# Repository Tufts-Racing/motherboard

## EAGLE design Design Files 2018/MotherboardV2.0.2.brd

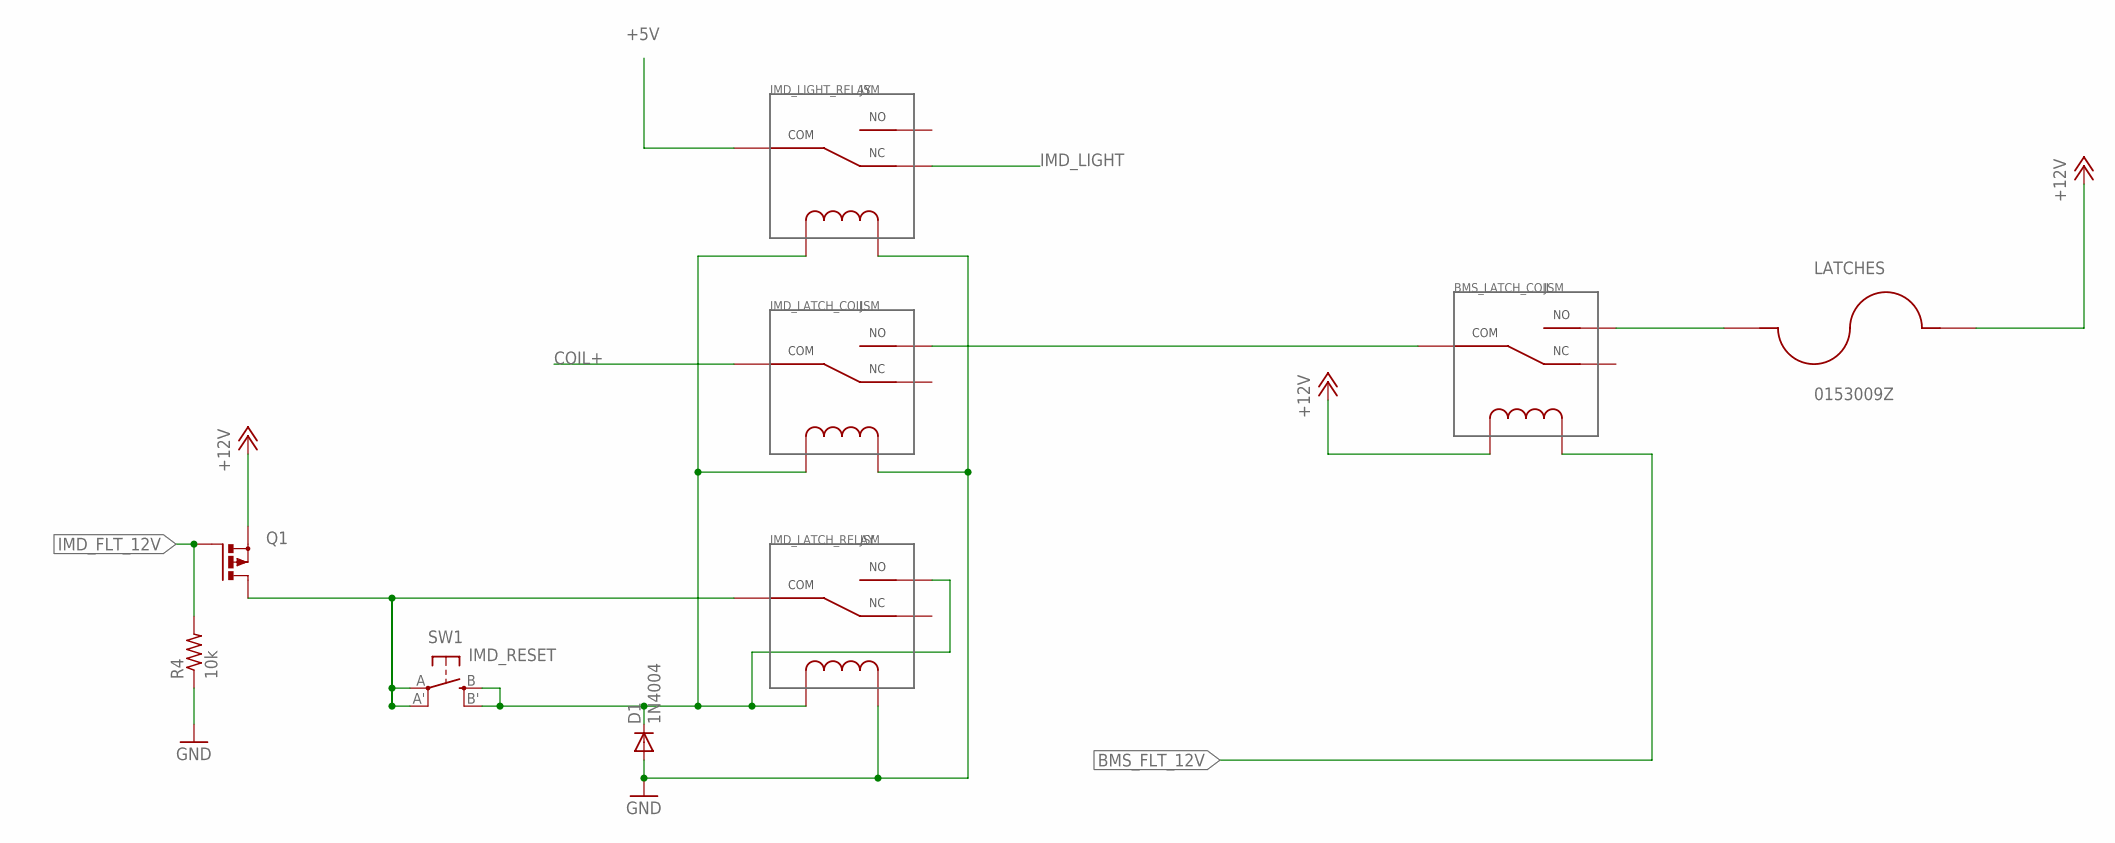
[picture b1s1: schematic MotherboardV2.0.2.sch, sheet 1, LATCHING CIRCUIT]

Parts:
BMS_LATCH_COIL: JSM; JS-M
D1: 1N4004; DO41-10
IMD_LATCH_COIL: JSM; JS-M
IMD_LATCH_RELAY: JSM; JS-M
IMD_LIGHT_RELAY: JSM; JS-M
LATCHES: 0153009Z; MINIFUSEHOLDER
Q1: PMOSFET_PTO220BV; TO220BV
R4: 10k; 0207/9
SW1: IMD_RESET; EVQ-Q2

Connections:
+5V: IMD_LIGHT_RELAY.COM; also elsewhere on the board
+12V: BMS_LATCH_COIL.COIL1, LATCHES.P$2, Q1.S; also elsewhere on the board
BMS_FLT_12V: BMS_LATCH_COIL.COIL2; also elsewhere on the board
COIL+: IMD_LATCH_COIL.COM; also elsewhere on the board
GND: D1.A, IMD_LATCH_COIL.COIL2, IMD_LATCH_RELAY.COIL2, IMD_LIGHT_RELAY.COIL2, R4.1; also elsewhere on the board
IMD_FLT_12V: Q1.G, R4.2; also elsewhere on the board
IMD_LATCH_SW1: IMD_LATCH_RELAY.COM, Q1.D, SW1.A, SW1.A' (P1)
IMD_LATCH_SW2: D1.C, IMD_LATCH_COIL.COIL1, IMD_LATCH_RELAY.COIL1, IMD_LATCH_RELAY.NO, IMD_LIGHT_RELAY.COIL1, SW1.B (S), SW1.B' (S1)
IMD_LIGHT: IMD_LIGHT_RELAY.NC; also elsewhere on the board
unnamed: BMS_LATCH_COIL.COM, IMD_LATCH_COIL.NO
unnamed: BMS_LATCH_COIL.NO, LATCHES.P$1

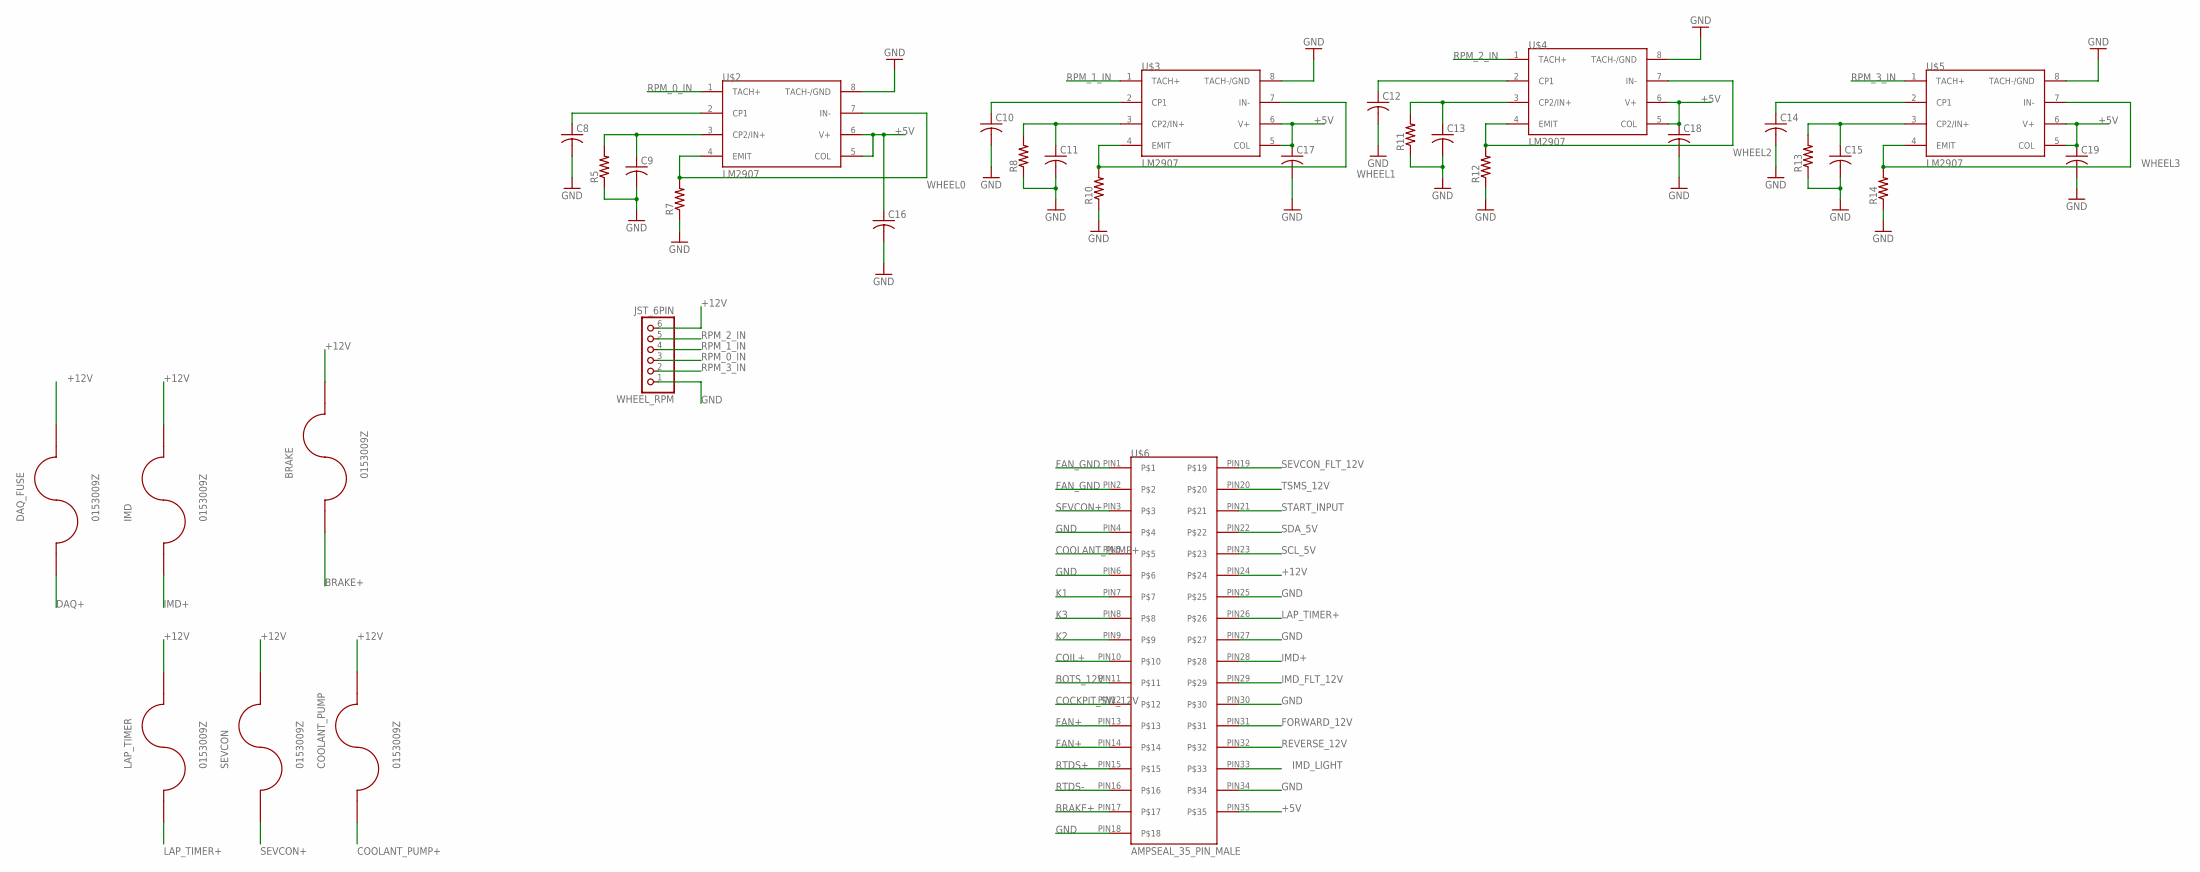
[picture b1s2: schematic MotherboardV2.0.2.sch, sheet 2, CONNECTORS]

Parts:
BRAKE: 0153009Z; MINIFUSEHOLDER
C8, C9, C10, C11, C12, C13, C14, C15, C16, C17, C18, C19: C-US050-024X044; C050-024X044
COOLANT_PUMP: 0153009Z; MINIFUSEHOLDER
DAQ_FUSE: 0153009Z; MINIFUSEHOLDER
IMD: 0153009Z; MINIFUSEHOLDER
LAP_TIMER: 0153009Z; MINIFUSEHOLDER
R5, R7, R8, R10, R11, R12, R13, R14: R-US_0309/V; 0309V
SEVCON: 0153009Z; MINIFUSEHOLDER
U$2, U$3, U$4, U$5: LM2907; DIL08
U$6: AMPSEAL_35_PIN_MALE
WHEEL_RPM: JST_6PIN; JST-PH-6-THM

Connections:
+5V: C16.1, C17.1, C18.1, C19.1, U$2.5 (COL), U$2.6 (V+), U$3.5 (COL), U$3.6 (V+), U$4.5 (COL), U$4.6 (V+), U$5.5 (COL), U$5.6 (V+), U$6.PIN35; also elsewhere on the board
+12V: BRAKE.P$2, COOLANT_PUMP.P$2, DAQ_FUSE.P$2, IMD.P$2, LAP_TIMER.P$2, SEVCON.P$2, U$6.PIN24, WHEEL_RPM.6; also elsewhere on the board
BOTS_12V: U$6.PIN11; also elsewhere on the board
BRAKE+: BRAKE.P$1, U$6.PIN17
COCKPIT_SW_12V: U$6.PIN12; also elsewhere on the board
COIL+: U$6.PIN10; also elsewhere on the board
COOLANT_PUMP+: COOLANT_PUMP.P$1, U$6.PIN5
DAQ+: DAQ_FUSE.P$1; also elsewhere on the board
FAN+: U$6.PIN13, U$6.PIN14; also elsewhere on the board
FAN_GND: U$6.PIN1, U$6.PIN2; also elsewhere on the board
FORWARD_12V: U$6.PIN31; also elsewhere on the board
GND: C8.2, C9.2, C10.2, C11.2, C12.2, C13.2, C14.2, C15.2, C16.2, C17.2, C18.2, C19.2, R5.1, R7.1, R8.1, R10.1, R11.1, R12.1, R13.1, R14.1, U$2.8 (TACH-/GND), U$3.8 (TACH-/GND), U$4.8 (TACH-/GND), U$5.8 (TACH-/GND), U$6.PIN4, U$6.PIN6, U$6.PIN18, U$6.PIN25, U$6.PIN27, U$6.PIN30, U$6.PIN34, WHEEL_RPM.1; also elsewhere on the board
IMD+: IMD.P$1, U$6.PIN28
IMD_FLT_12V: U$6.PIN29; also elsewhere on the board
IMD_LIGHT: U$6.PIN33; also elsewhere on the board
K1: U$6.PIN7; also elsewhere on the board
K2: U$6.PIN9; also elsewhere on the board
K3: U$6.PIN8; also elsewhere on the board
LAP_TIMER+: LAP_TIMER.P$1, U$6.PIN26
unnamed: C8.1, U$2.2 (CP1)
unnamed: C9.1, R5.2, U$2.3 (CP2/IN+)
unnamed: C10.1, U$3.2 (CP1)
unnamed: C11.1, R8.2, U$3.3 (CP2/IN+)
unnamed: C12.1, U$4.2 (CP1)
unnamed: C13.1, R11.2, U$4.3 (CP2/IN+)
unnamed: C14.1, U$5.2 (CP1)
unnamed: C15.1, R13.2, U$5.3 (CP2/IN+)
REVERSE_12V: U$6.PIN32; also elsewhere on the board
RPM_0_IN: U$2.1 (TACH+), WHEEL_RPM.3
RPM_1_IN: U$3.1 (TACH+), WHEEL_RPM.4
RPM_2_IN: U$4.1 (TACH+), WHEEL_RPM.5
RPM_3_IN: U$5.1 (TACH+), WHEEL_RPM.2
RTDS+: U$6.PIN15; also elsewhere on the board
RTDS-: U$6.PIN16; also elsewhere on the board
SCL_5V: U$6.PIN23; also elsewhere on the board
SDA_5V: U$6.PIN22; also elsewhere on the board
SEVCON+: SEVCON.P$1, U$6.PIN3
SEVCON_FLT_12V: U$6.PIN19; also elsewhere on the board
START_INPUT: U$6.PIN21; also elsewhere on the board
TSMS_12V: U$6.PIN20; also elsewhere on the board
WHEEL0: R7.2, U$2.4 (EMIT), U$2.7 (IN-); also elsewhere on the board
WHEEL1: R10.2, U$3.4 (EMIT), U$3.7 (IN-); also elsewhere on the board
WHEEL2: R12.2, U$4.4 (EMIT), U$4.7 (IN-); also elsewhere on the board
WHEEL3: R14.2, U$5.4 (EMIT), U$5.7 (IN-); also elsewhere on the board

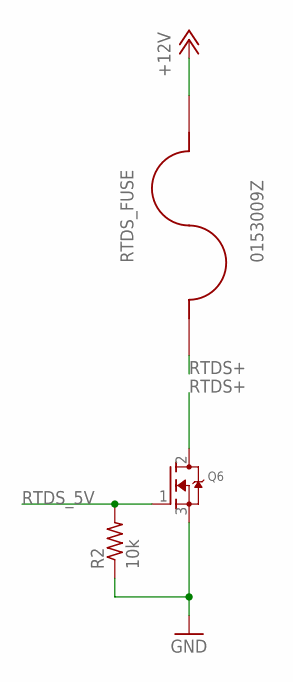
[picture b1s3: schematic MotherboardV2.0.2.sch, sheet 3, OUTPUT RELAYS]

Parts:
Q6: MOSFET-NGDS_TO220V; TO220V
R2: 10k; 0207/9
RTDS_FUSE: 0153009Z; MINIFUSEHOLDER

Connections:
+12V: RTDS_FUSE.P$2; also elsewhere on the board
GND: Q6.3 (S), R2.1; also elsewhere on the board
RTDS+: RTDS_FUSE.P$1; also elsewhere on the board
RTDS-: Q6.2 (D); also elsewhere on the board
RTDS_5V: Q6.1 (G), R2.2; also elsewhere on the board

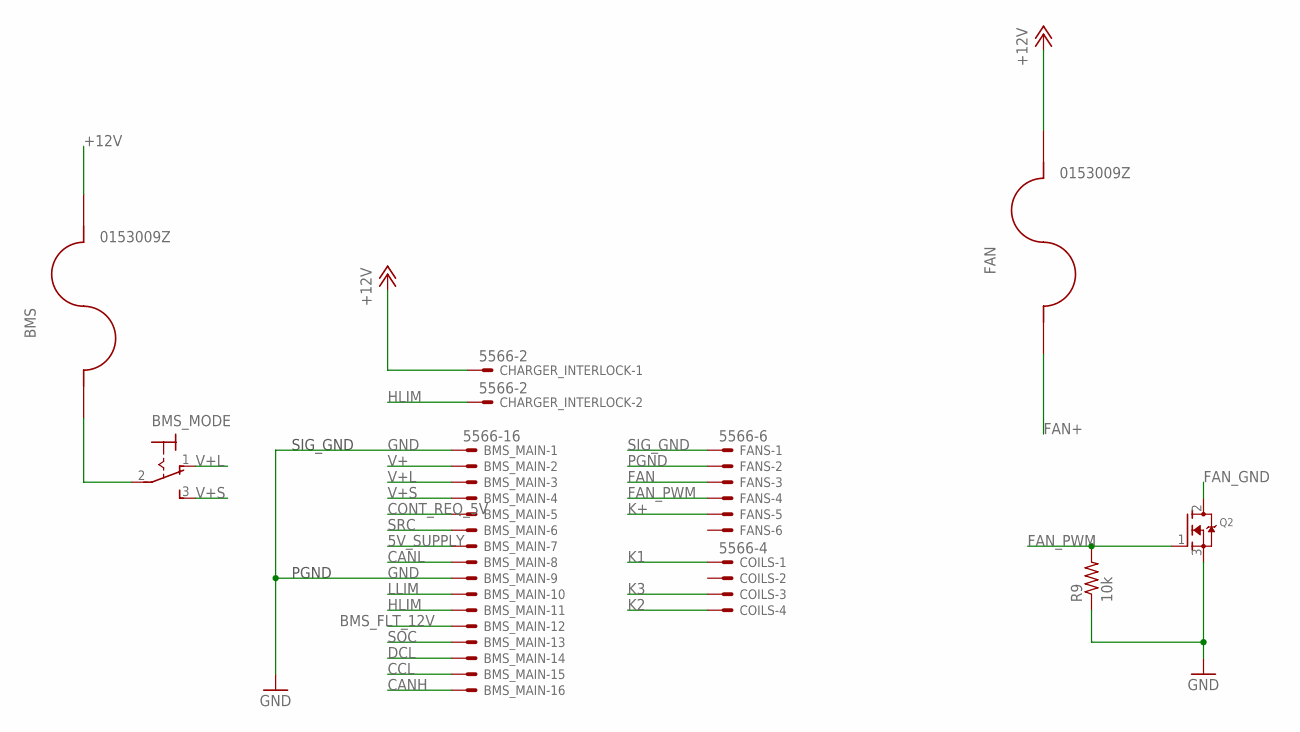
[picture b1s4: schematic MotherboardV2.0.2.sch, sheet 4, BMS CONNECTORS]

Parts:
BMS: 0153009Z; MINIFUSEHOLDER
BMS_MAIN: 5566-16
BMS_MODE: 320-916
CHARGER_INTERLOCK: 5566-2
COILS: 5566-4
FAN: 0153009Z; MINIFUSEHOLDER
FANS: 5566-6
Q2: MOSFET-NGDS_TO220V; TO220V
R9: 10k; 0207/9

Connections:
5V_SUPPLY: BMS_MAIN.7
+12V: BMS.P$2, CHARGER_INTERLOCK.1, FAN.P$2; also elsewhere on the board
BMS_FLT_12V: BMS_MAIN.12; also elsewhere on the board
CANH: BMS_MAIN.16
CANL: BMS_MAIN.8
CCL: BMS_MAIN.15
CONT_REQ_5V: BMS_MAIN.5; also elsewhere on the board
DCL: BMS_MAIN.14
FAN: FANS.3
FAN+: FAN.P$1; also elsewhere on the board
FAN_GND: Q2.2 (D); also elsewhere on the board
FAN_PWM: FANS.4, Q2.1 (G), R9.2
GND: BMS_MAIN.1, BMS_MAIN.9, Q2.3 (S), R9.1; also elsewhere on the board
HLIM: BMS_MAIN.11, CHARGER_INTERLOCK.2
K1: COILS.1; also elsewhere on the board
K2: COILS.4; also elsewhere on the board
K3: COILS.3; also elsewhere on the board
K+: FANS.5
LLIM: BMS_MAIN.10
unnamed: BMS.P$1, BMS_MODE.2
PGND: FANS.2
SIG_GND: FANS.1
SOC: BMS_MAIN.13; also elsewhere on the board
SRC: BMS_MAIN.6
V+: BMS_MAIN.2
V+L: BMS_MAIN.3, BMS_MODE.1 (O)
V+S: BMS_MAIN.4, BMS_MODE.3 (S)

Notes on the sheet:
SIG_GND
PGND

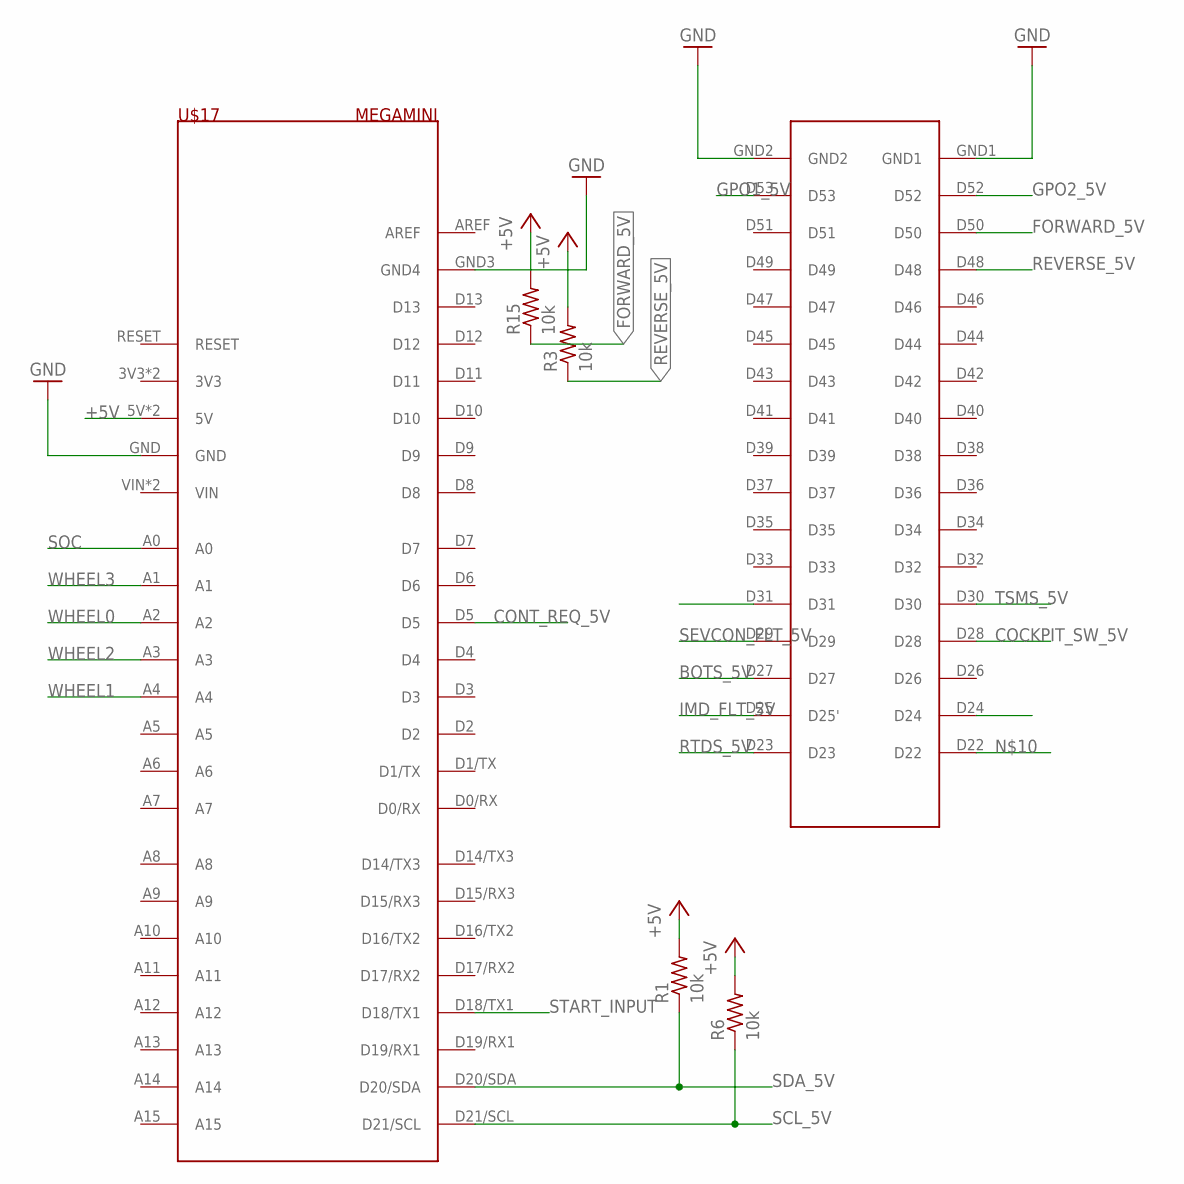
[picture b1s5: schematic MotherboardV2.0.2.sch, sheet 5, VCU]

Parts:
R1, R3, R6, R15: 10k; 0207/9
U$17: MEGAMINI

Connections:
+5V: R1.2, R3.2, R6.2, R15.2, U$17.5V, U$17.5V_2 (5V); also elsewhere on the board
BMS_FLT_5V: U$17.D31; also elsewhere on the board
BOTS_5V: U$17.D27; also elsewhere on the board
COCKPIT_SW_5V: U$17.D28; also elsewhere on the board
CONT_REQ_5V: U$17.D5; also elsewhere on the board
FORWARD_5V: R15.1, U$17.D50; also elsewhere on the board
GND: U$17.GND, U$17.GND1, U$17.GND2, U$17.GND3 (GND4); also elsewhere on the board
GPO1_5V: U$17.D53; also elsewhere on the board
GPO2_5V: U$17.D52; also elsewhere on the board
IMD_FLT_5V: U$17.D25 (D25'); also elsewhere on the board
REVERSE_5V: R3.1, U$17.D48; also elsewhere on the board
RTDS_5V: U$17.D23; also elsewhere on the board
SCL_5V: R6.1, U$17.D21/SCL; also elsewhere on the board
SDA_5V: R1.1, U$17.D20/SDA; also elsewhere on the board
SEVCON_FLT_5V: U$17.D29; also elsewhere on the board
SOC: U$17.A0; also elsewhere on the board
START_INPUT: U$17.D18/TX1; also elsewhere on the board
TSMS_5V: U$17.D30; also elsewhere on the board
WHEEL0: U$17.A2; also elsewhere on the board
WHEEL1: U$17.A4; also elsewhere on the board
WHEEL2: U$17.A3; also elsewhere on the board
WHEEL3: U$17.A1; also elsewhere on the board

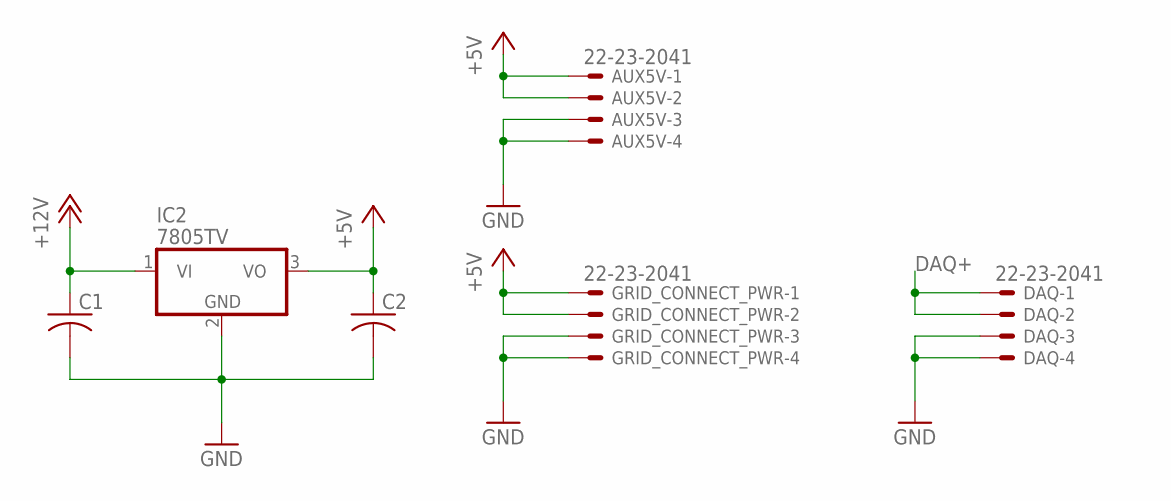
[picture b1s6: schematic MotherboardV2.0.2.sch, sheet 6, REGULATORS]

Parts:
AUX5V: 22-23-2041
C1, C2: C-US050-024X044; C050-024X044
DAQ: 22-23-2041
GRID_CONNECT_PWR: 22-23-2041
IC2: 7805TV; TO220V

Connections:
+5V: AUX5V.1, AUX5V.2, C2.1, GRID_CONNECT_PWR.1, GRID_CONNECT_PWR.2, IC2.3 (VO); also elsewhere on the board
+12V: C1.1, IC2.1 (VI); also elsewhere on the board
DAQ+: DAQ.1, DAQ.2; also elsewhere on the board
GND: AUX5V.3, AUX5V.4, C1.2, C2.2, DAQ.3, DAQ.4, GRID_CONNECT_PWR.3, GRID_CONNECT_PWR.4, IC2.2 (GND); also elsewhere on the board

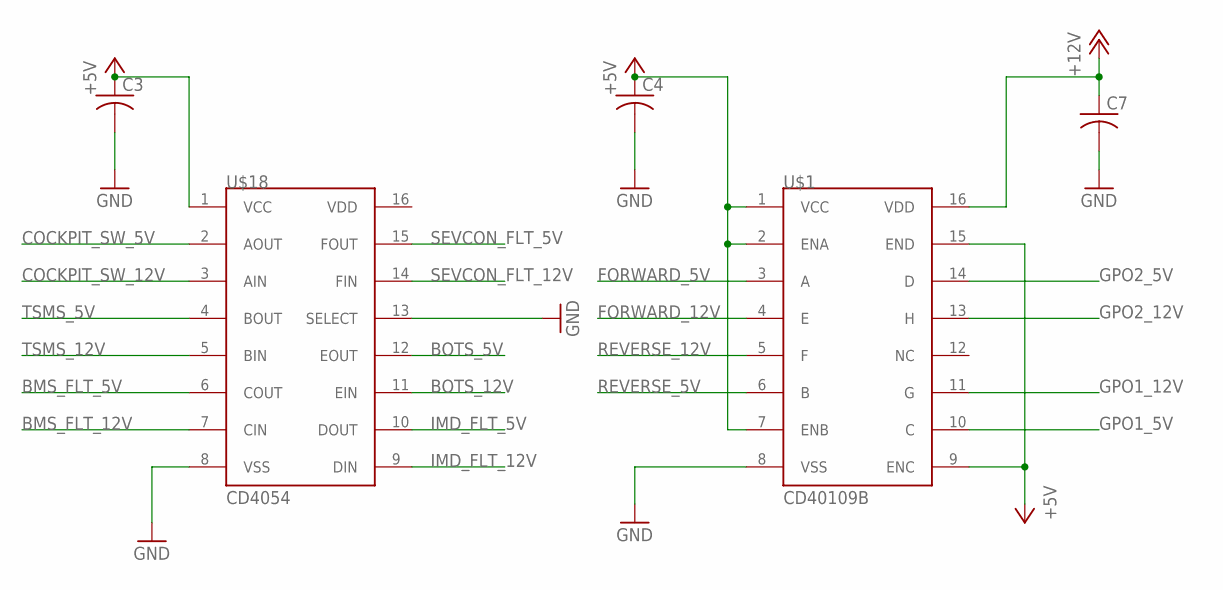
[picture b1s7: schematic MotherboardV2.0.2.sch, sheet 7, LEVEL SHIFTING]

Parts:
C3, C4, C7: C-US050-024X044; C050-024X044
U$1: CD40109B; DIL16
U$18: CD4054; DIL16

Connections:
+5V: C3.1, C4.1, U$1.1 (VCC), U$1.2 (ENA), U$1.7 (ENB), U$1.9 (ENC), U$1.15 (END), U$18.1 (VCC); also elsewhere on the board
+12V: C7.1, U$1.16 (VDD); also elsewhere on the board
BMS_FLT_5V: U$18.6 (COUT); also elsewhere on the board
BMS_FLT_12V: U$18.7 (CIN); also elsewhere on the board
BOTS_5V: U$18.12 (EOUT); also elsewhere on the board
BOTS_12V: U$18.11 (EIN); also elsewhere on the board
COCKPIT_SW_5V: U$18.2 (AOUT); also elsewhere on the board
COCKPIT_SW_12V: U$18.3 (AIN); also elsewhere on the board
FORWARD_5V: U$1.3 (A); also elsewhere on the board
FORWARD_12V: U$1.4 (E); also elsewhere on the board
GND: C3.2, C4.2, C7.2, U$1.8 (VSS), U$18.8 (VSS), U$18.13 (SELECT); also elsewhere on the board
GPO1_5V: U$1.10 (C); also elsewhere on the board
GPO1_12V: U$1.11 (G)
GPO2_5V: U$1.14 (D); also elsewhere on the board
GPO2_12V: U$1.13 (H)
IMD_FLT_5V: U$18.10 (DOUT); also elsewhere on the board
IMD_FLT_12V: U$18.9 (DIN); also elsewhere on the board
REVERSE_5V: U$1.6 (B); also elsewhere on the board
REVERSE_12V: U$1.5 (F); also elsewhere on the board
SEVCON_FLT_5V: U$18.15 (FOUT); also elsewhere on the board
SEVCON_FLT_12V: U$18.14 (FIN); also elsewhere on the board
TSMS_5V: U$18.4 (BOUT); also elsewhere on the board
TSMS_12V: U$18.5 (BIN); also elsewhere on the board

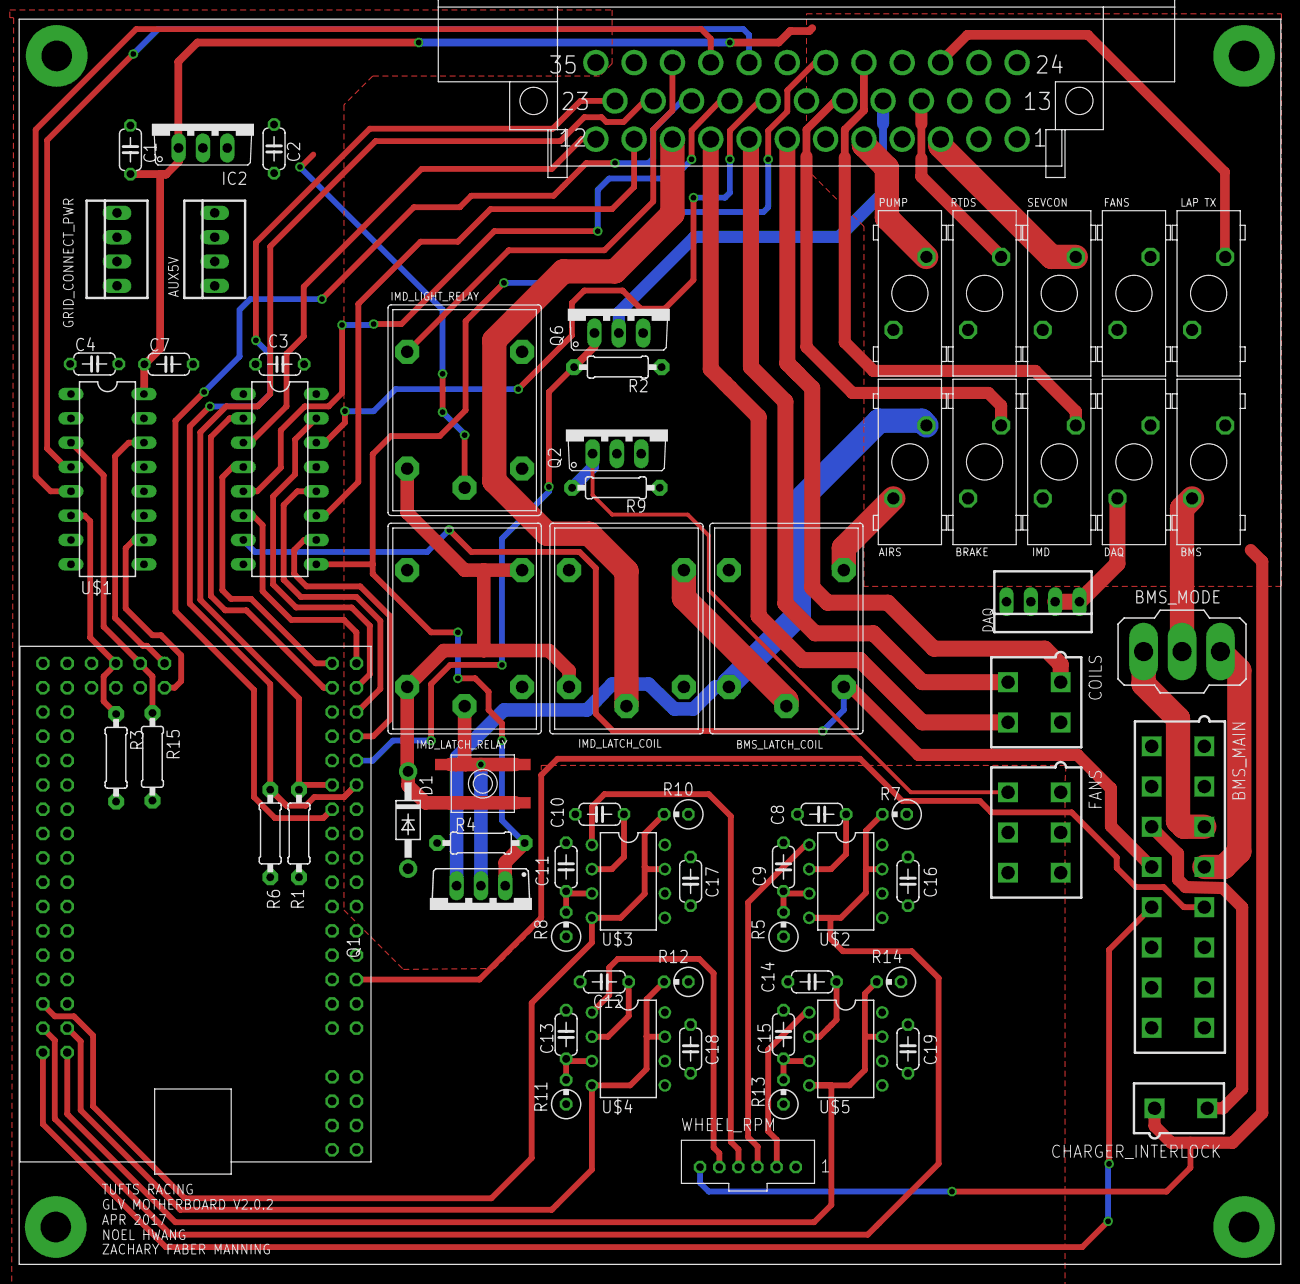
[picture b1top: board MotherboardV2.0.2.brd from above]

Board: 2 copper layers, 131.8 x 130.0 mm, 69 parts (0 on the bottom side), 67 nets.

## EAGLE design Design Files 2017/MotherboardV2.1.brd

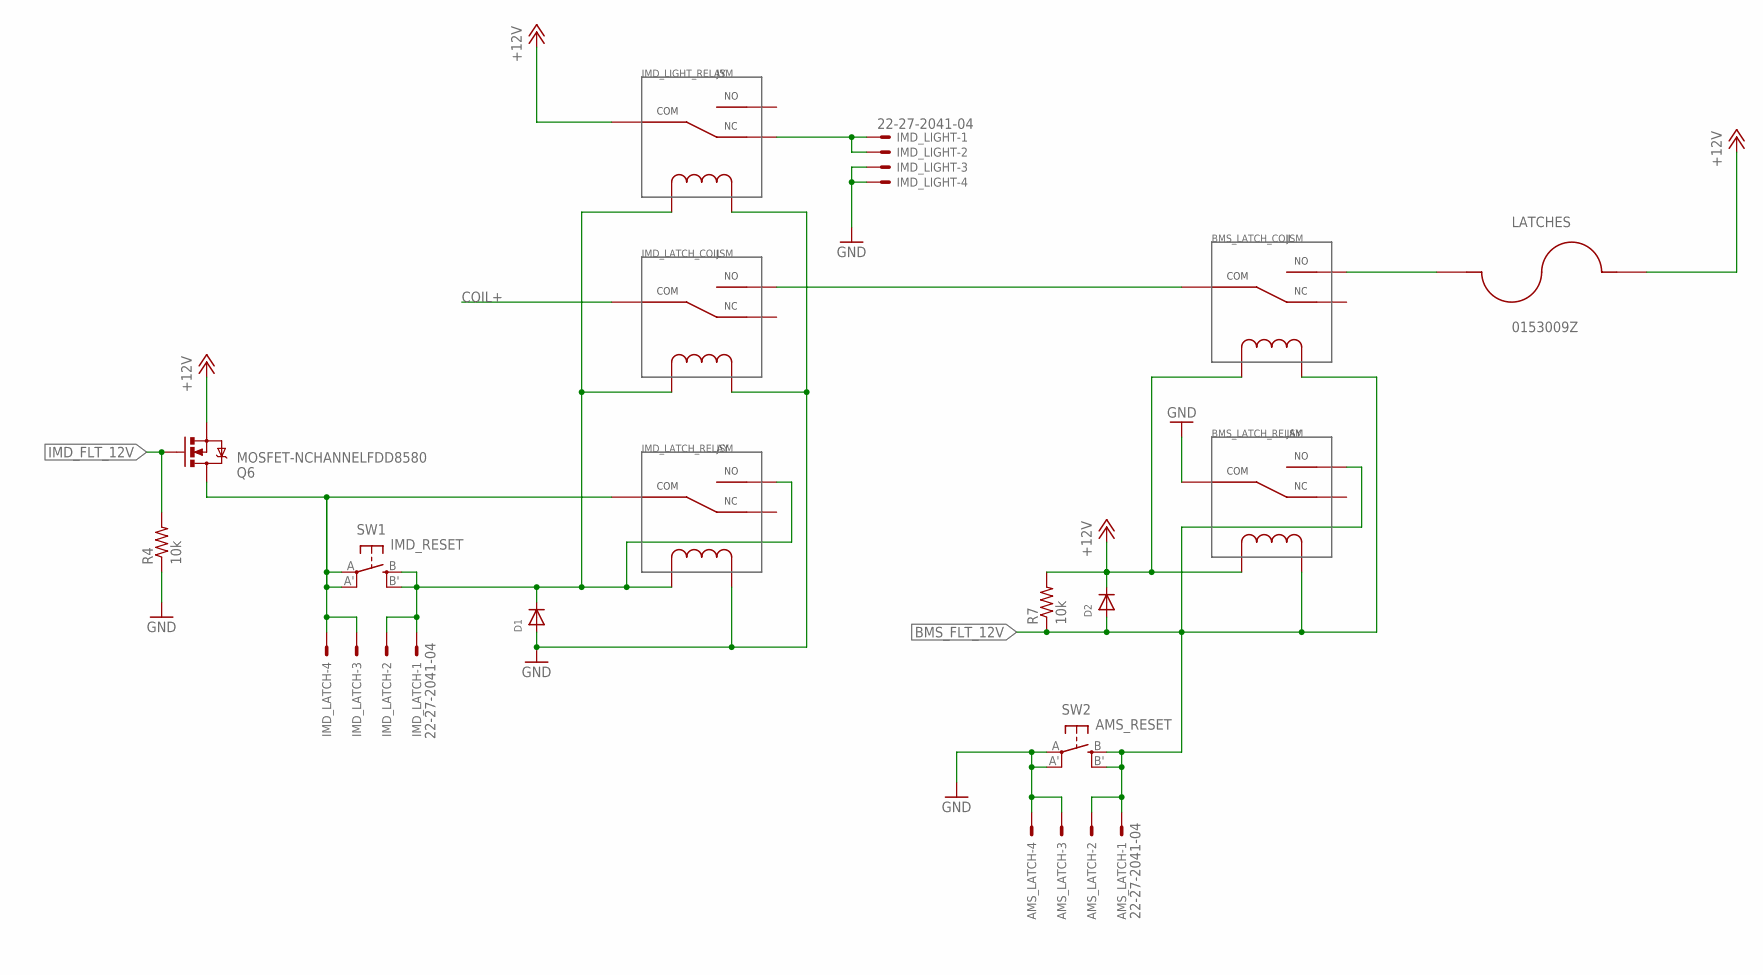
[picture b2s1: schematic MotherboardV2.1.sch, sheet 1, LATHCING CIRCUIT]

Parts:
AMS_LATCH: 22-27-2041-04; 6410-04
BMS_LATCH_COIL: JSM; JS-M
BMS_LATCH_RELAY: JSM; JS-M
D1, D2: DIODESOD-123; SOD-123
IMD_LATCH: 22-27-2041-04; 6410-04
IMD_LATCH_COIL: JSM; JS-M
IMD_LATCH_RELAY: JSM; JS-M
IMD_LIGHT: 22-27-2041-04; 6410-04
IMD_LIGHT_RELAY: JSM; JS-M
LATCHES: 0153009Z; MINIFUSEHOLDER
Q6: MOSFET-NCHANNELFDD8580; DPAK
R4, R7: 10k; M0805
SW1: IMD_RESET; EVQ-Q2
SW2: AMS_RESET; EVQ-Q2

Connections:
+12V: BMS_LATCH_COIL.COIL1, BMS_LATCH_RELAY.COIL1, D2.C, IMD_LIGHT_RELAY.COM, LATCHES.P$2, Q6.3 (S), R7.2; also elsewhere on the board
BMS_FLT_12V: AMS_LATCH.1, AMS_LATCH.2, BMS_LATCH_COIL.COIL2, BMS_LATCH_RELAY.COIL2, BMS_LATCH_RELAY.NO, D2.A, R7.1, SW2.B (S), SW2.B' (S1); also elsewhere on the board
COIL+: IMD_LATCH_COIL.COM; also elsewhere on the board
GND: AMS_LATCH.3, AMS_LATCH.4, BMS_LATCH_RELAY.COM, D1.A, IMD_LATCH_COIL.COIL2, IMD_LATCH_RELAY.COIL2, IMD_LIGHT.3, IMD_LIGHT.4, IMD_LIGHT_RELAY.COIL2, R4.1, SW2.A, SW2.A' (P1); also elsewhere on the board
IMD_FLT_12V: Q6.1 (G), R4.2; also elsewhere on the board
IMD_LATCH_SW1: IMD_LATCH.3, IMD_LATCH.4, IMD_LATCH_RELAY.COM, Q6.4 (D), SW1.A, SW1.A' (P1); also elsewhere on the board
IMD_LATCH_SW2: D1.C, IMD_LATCH.1, IMD_LATCH.2, IMD_LATCH_COIL.COIL1, IMD_LATCH_RELAY.COIL1, IMD_LATCH_RELAY.NO, IMD_LIGHT_RELAY.COIL1, SW1.B (S), SW1.B' (S1); also elsewhere on the board
unnamed: BMS_LATCH_COIL.COM, IMD_LATCH_COIL.NO
unnamed: IMD_LIGHT.1, IMD_LIGHT.2, IMD_LIGHT_RELAY.NC
unnamed: BMS_LATCH_COIL.NO, LATCHES.P$1

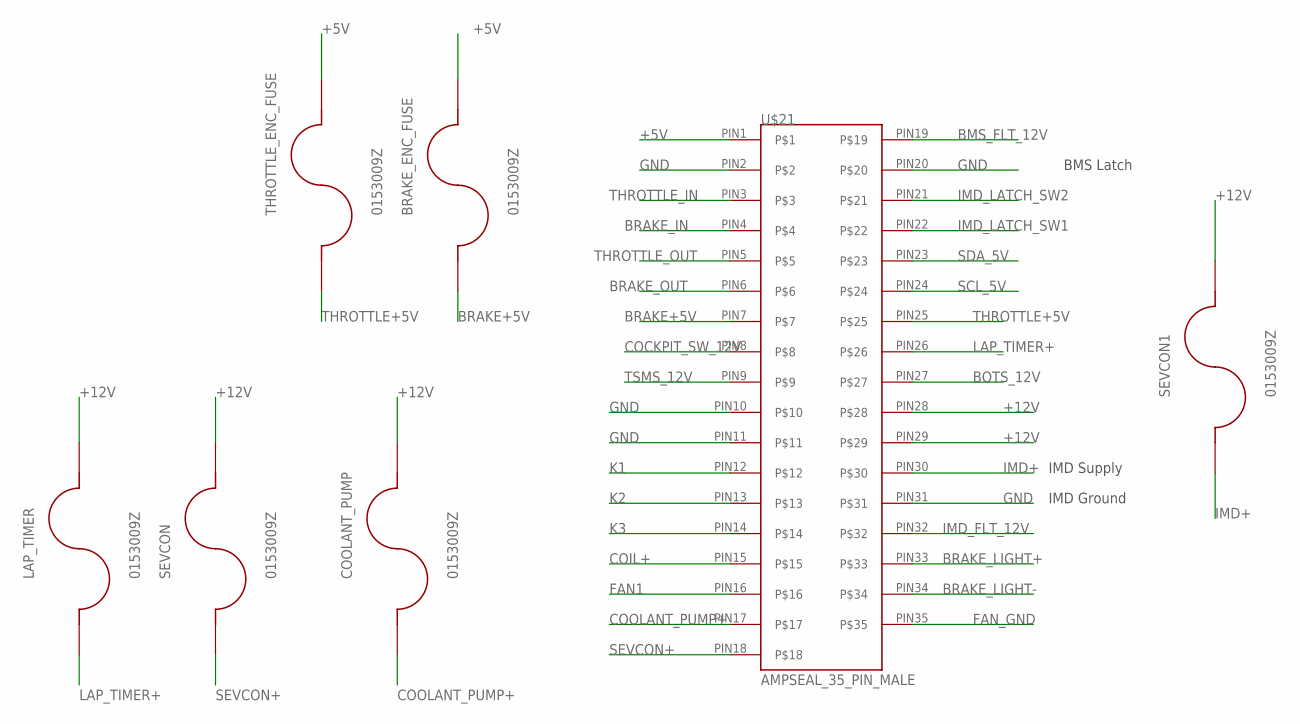
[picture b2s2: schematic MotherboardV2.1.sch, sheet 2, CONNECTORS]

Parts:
BRAKE_ENC_FUSE: 0153009Z; MINIFUSEHOLDER
COOLANT_PUMP: 0153009Z; MINIFUSEHOLDER
LAP_TIMER: 0153009Z; MINIFUSEHOLDER
SEVCON, SEVCON1: 0153009Z; MINIFUSEHOLDER
THROTTLE_ENC_FUSE: 0153009Z; MINIFUSEHOLDER
U$21: AMPSEAL_35_PIN_MALE

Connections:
+5V: BRAKE_ENC_FUSE.P$2, THROTTLE_ENC_FUSE.P$2, U$21.PIN1; also elsewhere on the board
+12V: COOLANT_PUMP.P$2, LAP_TIMER.P$2, SEVCON.P$2, SEVCON1.P$2, U$21.PIN28, U$21.PIN29; also elsewhere on the board
BMS_FLT_12V: U$21.PIN19; also elsewhere on the board
BOTS_12V: U$21.PIN27; also elsewhere on the board
BRAKE+5V: BRAKE_ENC_FUSE.P$1, U$21.PIN7
BRAKE_IN: U$21.PIN4
BRAKE_LIGHT+: U$21.PIN33; also elsewhere on the board
BRAKE_LIGHT-: U$21.PIN34; also elsewhere on the board
BRAKE_OUT: U$21.PIN6
COCKPIT_SW_12V: U$21.PIN8; also elsewhere on the board
COIL+: U$21.PIN15; also elsewhere on the board
COOLANT_PUMP+: COOLANT_PUMP.P$1, U$21.PIN17
FAN1: U$21.PIN16; also elsewhere on the board
FAN_GND: U$21.PIN35; also elsewhere on the board
GND: U$21.PIN2, U$21.PIN10, U$21.PIN11, U$21.PIN20, U$21.PIN31; also elsewhere on the board
IMD+: SEVCON1.P$1, U$21.PIN30
IMD_FLT_12V: U$21.PIN32; also elsewhere on the board
IMD_LATCH_SW1: U$21.PIN22; also elsewhere on the board
IMD_LATCH_SW2: U$21.PIN21; also elsewhere on the board
K1: U$21.PIN12; also elsewhere on the board
K2: U$21.PIN13; also elsewhere on the board
K3: U$21.PIN14; also elsewhere on the board
LAP_TIMER+: LAP_TIMER.P$1, U$21.PIN26
SCL_5V: U$21.PIN24; also elsewhere on the board
SDA_5V: U$21.PIN23; also elsewhere on the board
SEVCON+: SEVCON.P$1, U$21.PIN18
THROTTLE+5V: THROTTLE_ENC_FUSE.P$1, U$21.PIN25
THROTTLE_IN: U$21.PIN3
THROTTLE_OUT: U$21.PIN5
TSMS_12V: U$21.PIN9; also elsewhere on the board

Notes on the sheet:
BMS Latch
IMD Supply
IMD Ground

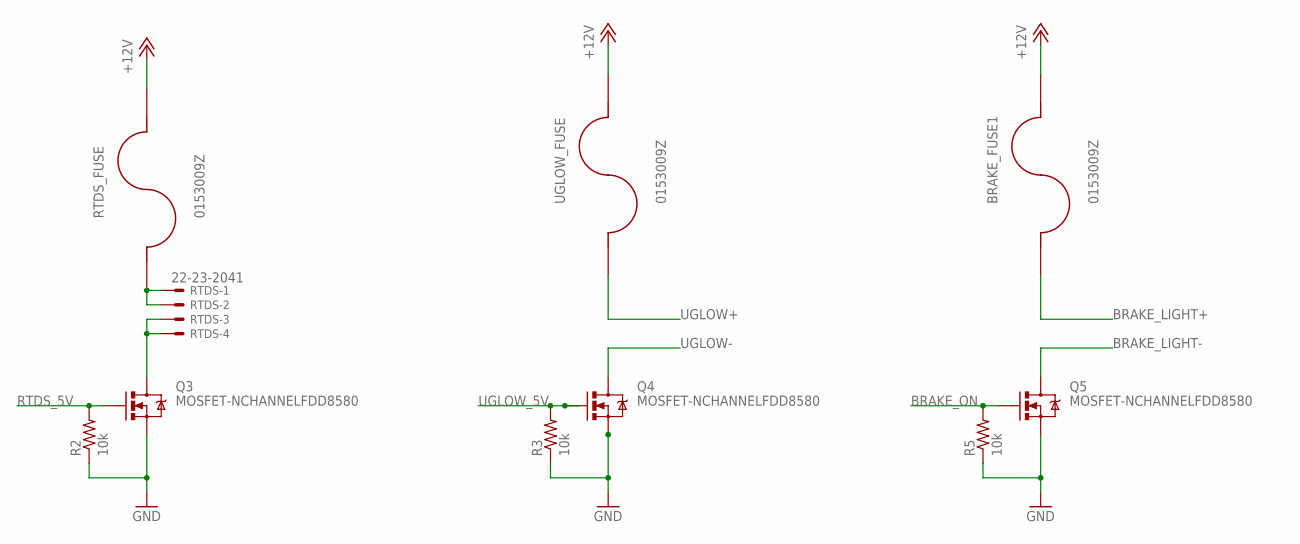
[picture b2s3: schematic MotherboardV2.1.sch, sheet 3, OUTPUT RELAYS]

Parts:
BRAKE_FUSE1: 0153009Z; MINIFUSEHOLDER
Q3, Q4, Q5: MOSFET-NCHANNELFDD8580; DPAK
R2, R3, R5: 10k; M0805
RTDS: 22-23-2041; MPN 22-23-2041
RTDS_FUSE: 0153009Z; MINIFUSEHOLDER
UGLOW_FUSE: 0153009Z; MINIFUSEHOLDER

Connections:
+12V: BRAKE_FUSE1.P$2, RTDS_FUSE.P$2, UGLOW_FUSE.P$2; also elsewhere on the board
BRAKE_LIGHT+: BRAKE_FUSE1.P$1; also elsewhere on the board
BRAKE_LIGHT-: Q5.4 (D); also elsewhere on the board
BRAKE_ON: Q5.1 (G), R5.2
GND: Q3.3 (S), Q4.3 (S), Q5.3 (S), R2.1, R3.1, R5.1; also elsewhere on the board
unnamed: Q3.4 (D), RTDS.3, RTDS.4
unnamed: RTDS.1, RTDS.2, RTDS_FUSE.P$1
RTDS_5V: Q3.1 (G), R2.2; also elsewhere on the board
UGLOW+: UGLOW_FUSE.P$1
UGLOW-: Q4.4 (D)
UGLOW_5V: Q4.1 (G), R3.2; also elsewhere on the board

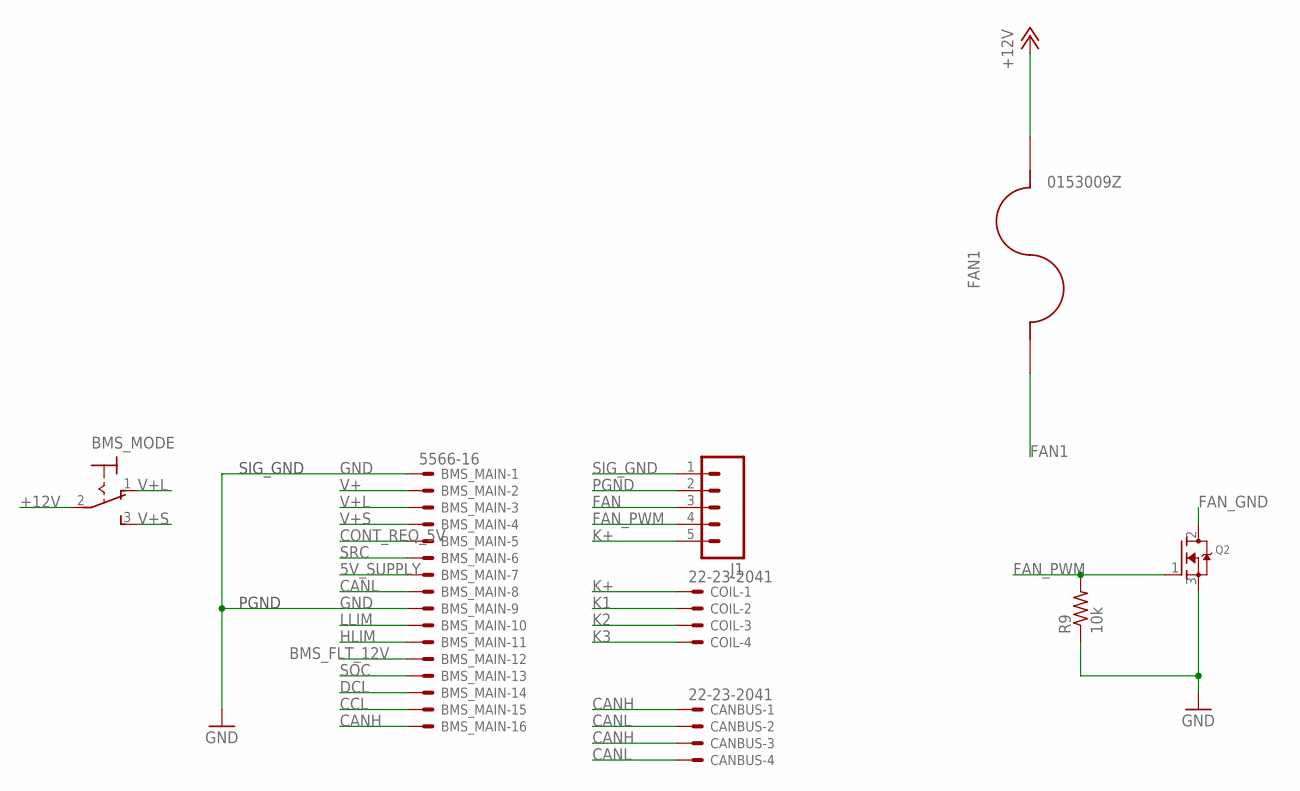
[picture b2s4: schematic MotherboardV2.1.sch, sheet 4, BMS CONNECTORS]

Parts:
BMS_MAIN: 5566-16
BMS_MODE: 320-916
CANBUS: 22-23-2041
COIL: 22-23-2041
FAN1: 0153009Z; MINIFUSEHOLDER
J1: M05LOCK; 1X05_LOCK
Q2: MOSFET-NGDS_TO220V; TO220V
R9: 10k; 0207/9

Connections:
5V_SUPPLY: BMS_MAIN.7
+12V: BMS_MODE.2, FAN1.P$2; also elsewhere on the board
BMS_FLT_12V: BMS_MAIN.12; also elsewhere on the board
CANH: BMS_MAIN.16, CANBUS.1, CANBUS.3
CANL: BMS_MAIN.8, CANBUS.2, CANBUS.4
CCL: BMS_MAIN.15
CONT_REQ_5V: BMS_MAIN.5; also elsewhere on the board
DCL: BMS_MAIN.14
FAN: J1.3
FAN1: FAN1.P$1; also elsewhere on the board
FAN_GND: Q2.2 (D); also elsewhere on the board
FAN_PWM: J1.4, Q2.1 (G), R9.2
GND: BMS_MAIN.1, BMS_MAIN.9, Q2.3 (S), R9.1; also elsewhere on the board
HLIM: BMS_MAIN.11
K1: COIL.2; also elsewhere on the board
K2: COIL.3; also elsewhere on the board
K3: COIL.4; also elsewhere on the board
K+: COIL.1, J1.5
LLIM: BMS_MAIN.10
PGND: J1.2
SIG_GND: J1.1
SOC: BMS_MAIN.13; also elsewhere on the board
SRC: BMS_MAIN.6
V+: BMS_MAIN.2
V+L: BMS_MAIN.3, BMS_MODE.1 (O)
V+S: BMS_MAIN.4, BMS_MODE.3 (S)

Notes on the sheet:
SIG_GND
PGND

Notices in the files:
parts and their libraries:
SparkFun-Aesthetics: Licensing: Creative Commons ShareAlike 4.0 International - https://creativecommons.org/licenses/by-sa/4.0
